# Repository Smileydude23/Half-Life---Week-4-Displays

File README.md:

# Half-Life---Week-4-Displays
My project for week 4 of Half Life, designing a display. This is both a clock, and an environmental sensor. The PCB has a 4-digit 7-segment display, a real time clock module (ds3231s), a temperature/humidity sensor(dht11), a rotary encoder for navigation between different menus (ec11), and a connector for a strip of RGB LEDs (NeoPixels). The wiring for this PCB is horrible because I just started connecting dots until they couldn't, switched to back copper to do more, then used vias when I couldn't connect anymore (vias are a goated wiring function). The PCB also has 2 LEDs to indicate whether the time is AM or PM.
| Part | Qty | Unit Price (USD) | Total (USD) | Vendor |
| :--- | :---: | :---: | :---: | :--- |
| **Seeeduino Seeed Studio XIAO ESP32-C3** <br> | 1 | $1.01 | $1.01 | Aliexpress |
| **DS3231 Real-Time Clock Chip IC** <br> | 1 | $2.50 | $2.50 | Aliexpress |
| **50pcs 50V10uf 5x11mm Aluminum Electrolytic Capacitor** <br>  | 1 | $2.38 | $2.38 | Aliexpress |
| **3MM 5MM Light Emitting Diodes Electronics Kit** <br> | 1 | $2.50 | $2.50 | Aliexpress |
| **0.56 Inch 12Pins 4 Digits 7 Segment Display** <br> | 1 | $1.01 | $1.01 | Aliexpress |
| **10PCS TM1637 DIP-20 LED Digital Tube Driver Chip** <br> | 1 | $3.19 | $3.19 | Aliexpress |
| **Pin Header Socket C Connector** <br> | 1 | $2.08 | $2.08 | Aliexpress |
| **20Pcs 50V Direct Insertion Aluminum Electrolytic Capacitor** <br> | 1 | $2.86 | $2.86 | Aliexpress |
| **WS2812B Led Lights DC5V Smart RGB Led Strip Light** <br> | 1 | $1.01 | $1.01 | Aliexpress |
| **PCB Manufacturing** <br> | 1 | $4.00 | $4.00 | JLCPCB |
| **Module 2X Dht 11 Digital Humidity, Temperature Sensor** <br> | 1 | $1.74 | $1.74 | Amazon |
| **Tax & shipping** <br> *for the whole order* | - | - | $3.41 | - |
| **Total Funding Used** | | | **$27.69** / $30.00 | |

(best artist of all time frfr)

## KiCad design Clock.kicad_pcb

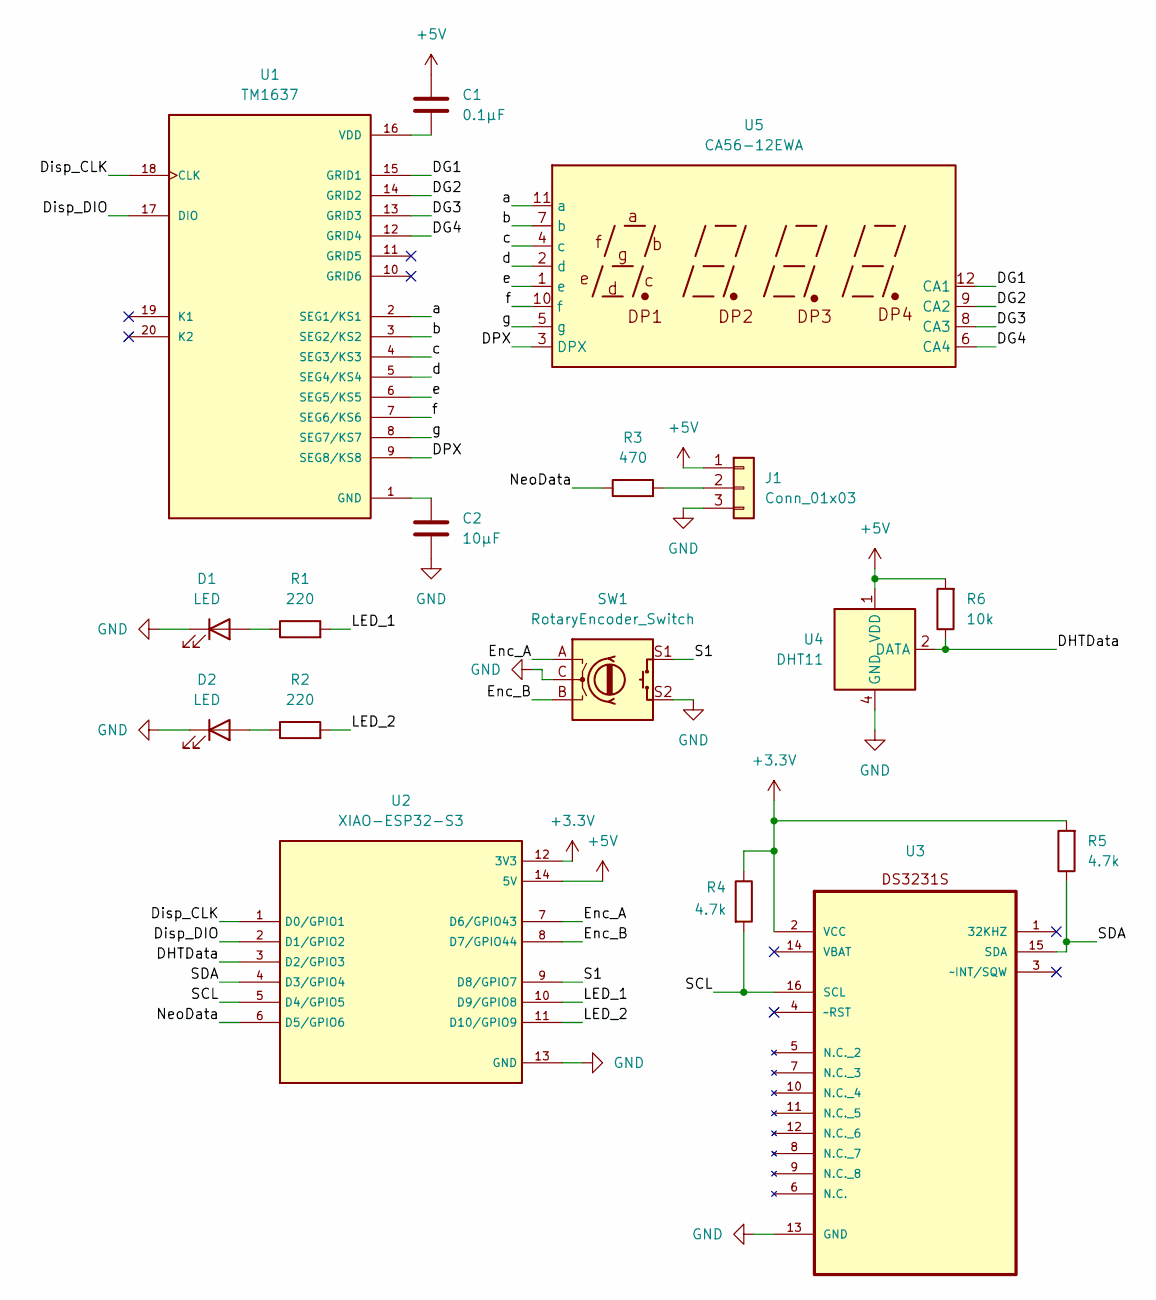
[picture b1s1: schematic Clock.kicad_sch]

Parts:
C1: 0.1µF; CP_Axial_L10.0mm_D4.5mm_P15.00mm_Horizontal
C2: 10µF; CP_Axial_L10.0mm_D4.5mm_P15.00mm_Horizontal
D1, D2: LED; LED_D5.0mm
J1: Conn_01x03; JST_XH_B3B-XH-A_1x03_P2.50mm_Vertical
R1, R2: 220; R_Axial_DIN0207_L6.3mm_D2.5mm_P7.62mm_Horizontal
R3: 470; R_Axial_DIN0207_L6.3mm_D2.5mm_P7.62mm_Horizontal
R4, R5: 4.7k; R_Axial_DIN0207_L6.3mm_D2.5mm_P7.62mm_Horizontal
R6: 10k; R_Axial_DIN0207_L6.3mm_D2.5mm_P7.62mm_Horizontal
SW1: RotaryEncoder_Switch; RotaryEncoder_Alps_EC11E-Switch_Vertical_H20mm
U1: TM1637; DIP778W43P254L2612H431Q20N; PARTREV v2.5
U2: XIAO-ESP32-S3; XIAO ESP32-S3; PARTREV April 22nd, 2026
U3: DS3231S
U4: DHT11; Aosong_DHT11_5.5x12.0_P2.54mm
U5: CA56-12EWA

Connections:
+3.3V: R4.1, R5.2, U2.12 (3V3), U3.2 (VCC)
+5V: C1.1, J1.1, R6.2, U2.14 (5V), U4.1 (VDD)
/DG1: U1.15 (GRID1), U5.12 (CA1)
/DG2: U1.14 (GRID2), U5.9 (CA2)
/DG3: U1.13 (GRID3), U5.8 (CA3)
/DG4: U1.12 (GRID4), U5.6 (CA4)
/DHTData: R6.1, U2.3 (D2/GPIO3), U4.2 (DATA)
/DPX: U1.9 (SEG8/KS8), U5.3 (DPX)
/Disp_CLK: U1.18 (CLK), U2.1 (D0/GPIO1)
/Disp_DIO: U1.17 (DIO), U2.2 (D1/GPIO2)
/Enc_A: SW1.A, U2.7 (D6/GPIO43)
/Enc_B: SW1.B, U2.8 (D7/GPIO44)
/LED_1: R1.2, U2.10 (D9/GPIO8)
/LED_2: R2.2, U2.11 (D10/GPIO9)
/NeoData: R3.1, U2.6 (D5/GPIO6)
/S1: SW1.S1, U2.9 (D8/GPIO7)
/SCL: R4.2, U2.5 (D4/GPIO5), U3.16 (SCL)
/SDA: R5.1, U2.4 (D3/GPIO4), U3.15 (SDA)
/a: U1.2 (SEG1/KS1), U5.11 (a)
/b: U1.3 (SEG2/KS2), U5.7 (b)
/c: U1.4 (SEG3/KS3), U5.4 (c)
/d: U1.5 (SEG4/KS4), U5.2 (d)
/e: U1.6 (SEG5/KS5), U5.1 (e)
/f: U1.7 (SEG6/KS6), U5.10 (f)
/g: U1.8 (SEG7/KS7), U5.5 (g)
GND: C2.2, D1.1 (K), D2.1 (K), J1.3, SW1.C, SW1.S2, U2.13 (GND), U3.13 (GND), U4.4 (GND)
unnamed: D1.2 (A), R1.1
unnamed: D2.2 (A), R2.1
unnamed: J1.2, R3.2
unnamed: C2.1, U1.1 (GND)
unnamed: C1.2, U1.16 (VDD)

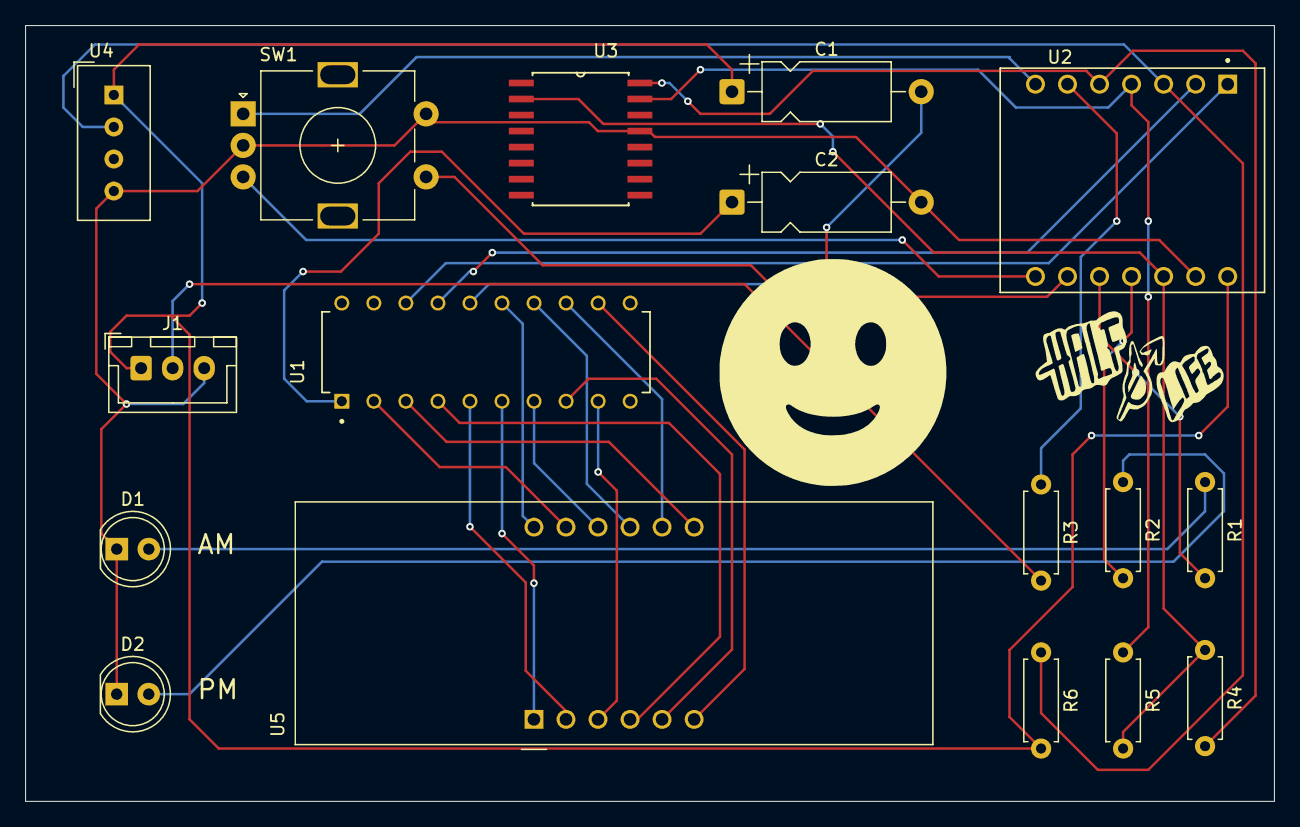
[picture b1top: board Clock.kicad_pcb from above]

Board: 2 copper layers, 99.0 x 61.5 mm, 17 parts (0 on the bottom side), 31 nets.

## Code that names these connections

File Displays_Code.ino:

#include <Wire.h>
#include <DHT.h>
#include <RTClib.h>
#include <TM1637Display.h>
#include <Adafruit_NeoPixel.h>

#define PIN_DISP_CLK  1    
#define PIN_DISP_DIO  2    
#define PIN_DHTDATA   3    
#define PIN_SDA       4    
#define PIN_SCL       5    
#define PIN_NEODATA   6    

#define PIN_ENC_A     7   
#define PIN_ENC_B     8    
#define PIN_S1        9    // (Encoder Button)
#define PIN_LED_1     10   // (AM LED)
#define PIN_LED_2     11   // (PM LED)

#define DHTTYPE DHT11
#define NUM_PIXELS 20      // Set this to actual NeoPixel strip count when I get the strip

DHT dht(PIN_DHTDATA, DHTTYPE);
RTC_DS3231 rtc;
TM1637Display display(PIN_DISP_CLK, PIN_DISP_DIO);
Adafruit_NeoPixel strip(NUM_PIXELS, PIN_NEODATA, NEO_GRB + NEO_KHZ800);

enum DisplayMode { TIME_MODE, TEMP_MODE, HUMID_MODE };
DisplayMode currentMode = TIME_MODE;

unsigned long modeSwitchTime = 0;
const unsigned long RETURN_TO_TIME_TIMEOUT = 15000;

int lastEncAState;
int brightnessLevel = 4; 

int lastButtonState = HIGH;
unsigned long lastDebounceTime = 0;
const unsigned long DEBOUNCE_DELAY = 50;

unsigned long lastDisplayUpdate = 0;
unsigned long lastRainbowUpdate = 0;
uint16_t rainbowHue = 0;
bool colonBlink = true;

void setup() {
  Serial.begin(115200);

  pinMode(PIN_ENC_A, INPUT_PULLUP);
  pinMode(PIN_ENC_B, INPUT_PULLUP);
  pinMode(PIN_S1, INPUT_PULLUP);
  
  pinMode(PIN_LED_1, OUTPUT);
  pinMode(PIN_LED_2, OUTPUT);

  Wire.begin(PIN_SDA, PIN_SCL);
  dht.begin();
  display.setBrightness(brightnessLevel);
  strip.begin();
  strip.show();

  if (!rtc.begin()) {
    Serial.println("Couldn't find RTC module!");
  }
  
  if (rtc.lostPower()) {
  rtc.adjust(DateTime(F(__DATE__), F(__TIME__)));
}

  lastEncAState = digitalRead(PIN_ENC_A);
}

void loop() {
  handleEncoder();
  handleButton();
  updateDisplayAndLEDs();
  updateRainbowBorder();
}


void handleEncoder() {
  int currentEncAState = digitalRead(PIN_ENC_A);
  
  if (currentEncAState != lastEncAState && currentEncAState == LOW) {
    if (digitalRead(PIN_ENC_B) != currentEncAState) {
      if (brightnessLevel < 7) brightnessLevel++;
    } else {
      if (brightnessLevel > 1) brightnessLevel--;
    }
    
    display.setBrightness(brightnessLevel);
    Serial.print("Brightness Level Updated: ");
    Serial.println(brightnessLevel);
  }
  lastEncAState = currentEncAState;
}

void handleButton() {
  int reading = digitalRead(PIN_S1);

  if (reading != lastButtonState) {
    lastDebounceTime = millis();
  }

  if ((millis() - lastDebounceTime) > DEBOUNCE_DELAY) {
    static int stableButtonState = HIGH;
    if (reading != stableButtonState) {
      stableButtonState = reading;

      if (stableButtonState == LOW) {
        modeSwitchTime = millis(); 
        
        if (currentMode == TIME_MODE) {
          currentMode = TEMP_MODE;
        } else if (currentMode == TEMP_MODE) {
          currentMode = HUMID_MODE;
        } else {
          currentMode = TIME_MODE;
        }
      }
    }
  }
  lastButtonState = reading;

  if (currentMode != TIME_MODE && (millis() - modeSwitchTime >= RETURN_TO_TIME_TIMEOUT)) {
    currentMode = TIME_MODE;
  }
}

void updateDisplayAndLEDs() {
  if (millis() - lastDisplayUpdate < 250) return; 
  lastDisplayUpdate = millis();

  DateTime now = rtc.now();

  int hour12 = now.hour();
  bool isPM = false;
  
  if (hour12 >= 12) {
    isPM = true;
    if (hour12 > 12) hour12 -= 12;
  }
  if (hour12 == 0) hour12 = 12;

  if (currentMode == TIME_MODE) {
    digitalWrite(PIN_LED_1, !isPM ? HIGH : LOW);
    digitalWrite(PIN_LED_2, isPM ? HIGH : LOW);

    colonBlink = !colonBlink; 
    int displayValue = (hour12 * 100) + now.minute();
    display.showNumberDecEx(displayValue, colonBlink ? 0b01000000 : 0, true);

  } else if (currentMode == TEMP_MODE) {
    digitalWrite(PIN_LED_1, LOW);
    digitalWrite(PIN_LED_2, LOW);

    float tempC = dht.readTemperature();
    if (isnan(tempC)) tempC = 0;
    int temp = (int)tempC;


    uint8_t data[] = {
      display.encodeDigit(tempC / 10),
      display.encodeDigit(tempC % 10),
      0x00,       // Blank spacer panel
      0b00111001  // Letter 'C'
    };
    display.setSegments(data);

  } else if (currentMode == HUMID_MODE) {
    digitalWrite(PIN_LED_1, LOW);
    digitalWrite(PIN_LED_2, LOW);

    float humidity = dht.readHumidity();
    if (isnan(humidity)) humidity = 0;
    int hum = (int)humidity;


    uint8_t data[] = {
      display.encodeDigit(humidity / 10),
      display.encodeDigit(humidity % 10),
      0x00,       // Blank spacer panel
      0b01110110  // Letter 'H'
    };
    display.setSegments(data);
  }
}

void updateRainbowBorder() {
  if (millis() - lastRainbowUpdate < 20) return;
  lastRainbowUpdate = millis();

  strip.setBrightness(brightnessLevel * 25);

  for (int i = 0; i < strip.numPixels(); i++) {
    int pixelHue = rainbowHue + (i * 65536L / strip.numPixels());
    strip.setPixelColor(i, strip.gamma32(strip.ColorHSV(pixelHue)));
  }
  strip.show();
  
  rainbowHue += 256;
}
